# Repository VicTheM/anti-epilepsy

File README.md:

# Anti-Epilepsy Fast Response Device

## Hardware

### System schematic

### 3D PCB view

### Enclosure prototype

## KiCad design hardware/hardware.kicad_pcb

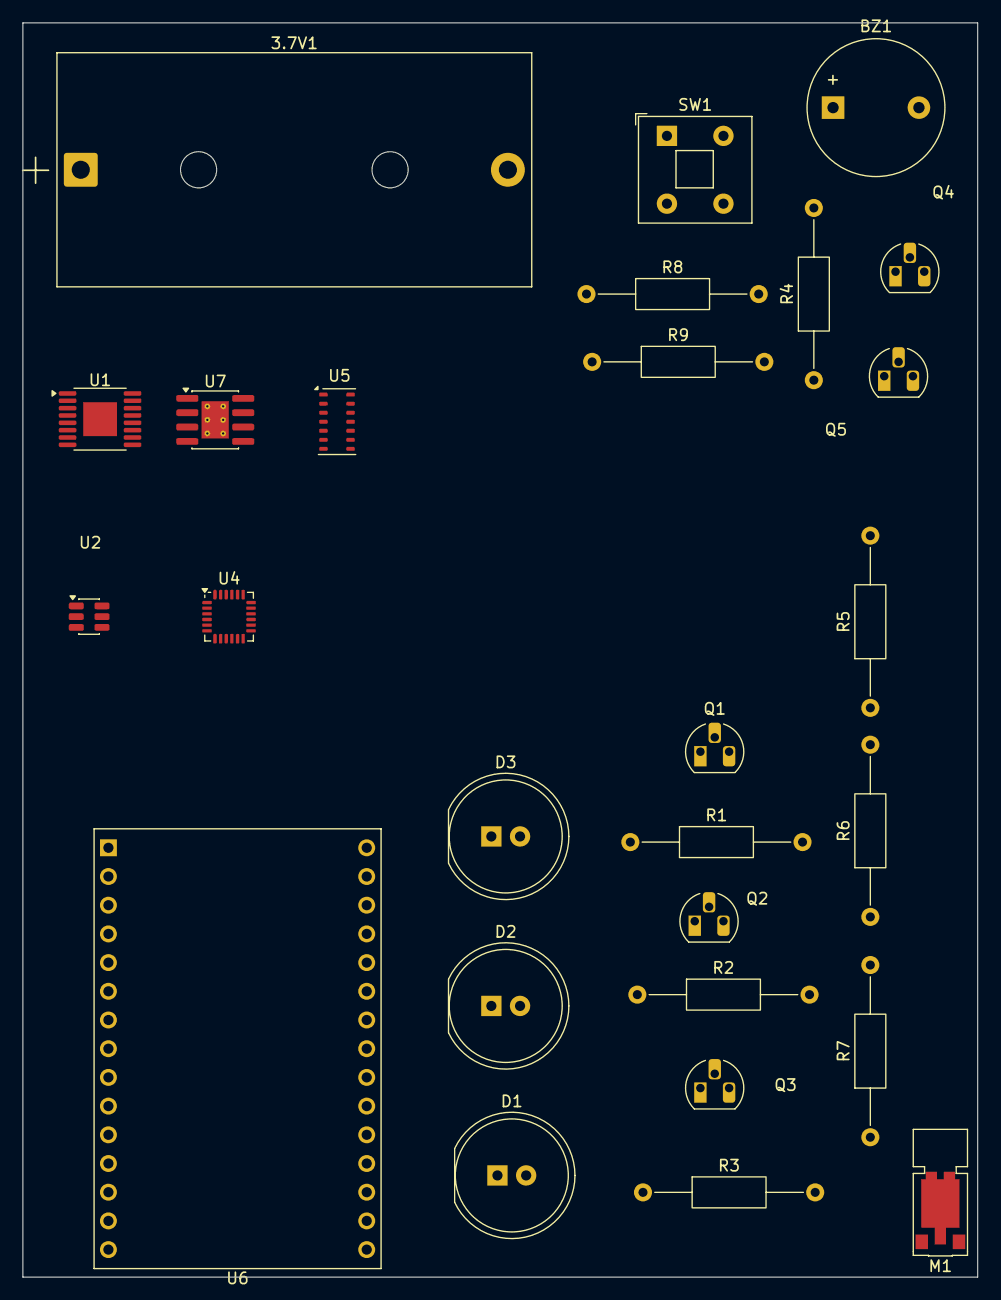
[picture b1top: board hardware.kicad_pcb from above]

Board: 2 copper layers, 84.5 x 111.0 mm, 27 parts (0 on the bottom side), 30 nets, no tracks yet.

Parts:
3.7V1: Battery; BatteryHolder_Bulgin_BX0123_1xCR123
BZ1: Buzzer; Buzzer_12x9.5RM7.6
D1, D2, D3: LED; LED_D10.0mm
M1: Motor_DC; Vybronics_VZ30C1T8219732L
Q1, Q2, Q3, Q5: 2N2219; TO-92L_HandSolder
Q4: Q_NPN_Darlington_BCEC; TO-92L_HandSolder
R1, R2, R6, R9: 220R; R_Axial_DIN0207_L6.3mm_D2.5mm_P15.24mm_Horizontal
R3, R4, R5, R7, R8: 1K; R_Axial_DIN0207_L6.3mm_D2.5mm_P15.24mm_Horizontal
SW1: SW_SPST; SW_Push_2P1T_Toggle_CK_PVA1xxH4xxxxxxV2
U1: A4954; TSSOP-16-1EP_4.4x5mm_P0.65mm_EP3x3mm
U2: TMP100; SOT-23-6
U4: MPU-6050; InvenSense_QFN-24_4x4mm_P0.5mm
U5: MAX30102; Maxim_OLGA-14_3.3x5.6mm_P0.8mm
U6: ESP32-S2-WROVER; ESP32-C3-DevKitM-1
U7: CN3158; SOIC-8-1EP_3.9x4.9mm_P1.27mm_EP2.41x3.3mm_ThermalVias

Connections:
+5V: BZ1.1 (+), D1.2 (A), D2.2 (A), D3.2 (A), M1.1 (+), SW1.2 (B), U2.4 (V+), U4.13 (VDD), U5.11 (VDD)
GND: 3.7V1.2 (-), Q4.3 (E), R1.2, R2.1, R6.2, R9.2, U2.2 (GND), U4.18 (GND), U5.12 (GND), U6.1 (GND), U6.26 (GND), U7.3 (GND), U7.9 (GND)
unnamed: 3.7V1.1 (+), U7.4 (VIN)
unnamed: BZ1.2 (-), Q1.3 (C)
unnamed: D1.1 (K), Q2.3 (C)
unnamed: D2.1 (K), Q3.3 (C)
unnamed: D3.1 (K), Q5.3 (C)
unnamed: M1.2 (-), Q4.2 (C)
unnamed: Q1.2 (B), R4.2
unnamed: Q1.1 (E), R2.2
unnamed: Q2.2 (B), R3.2
unnamed: Q2.1 (E), R1.1
unnamed: Q3.2 (B), R5.2
unnamed: Q3.1 (E), R6.1
unnamed: Q4.1 (B), R7.2
unnamed: Q5.2 (B), R8.2
unnamed: Q5.1 (E), R9.1
unnamed: SW1.1 (A), U7.5 (BAT)
unnamed: U1.1 (GND), U1.8 (GND), U1.17 (GND)
unnamed: U1.6 (IN1), U6.25 (IO26)
unnamed: U1.5 (IN2), U6.24 (IO21)
unnamed: U1.3 (IN3), U6.19 (IO16)
unnamed: U1.4 (IN4), U6.18 (IO15)
unnamed: U1.9 (VBB), U1.16 (VBB)
unnamed: U2.1 (SCL), U4.23 (SCL), U5.2 (SCL), U6.20 (IO17), U6.21 (IO18)
unnamed: U2.6 (SDA), U4.24 (SDA), U5.3 (SDA)
unnamed: U5.9 (VLED+), U5.10 (VLED+)
unnamed: R5.1, U6.27 (IO33)
unnamed: R8.1, U6.28 (IO34)
unnamed: R3.1, U6.29 (IO35)

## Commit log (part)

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2025-08-22 Circuit design setup
2025-08-22 Added libraries for accelerometer, gyrometer and heartbeat rate sensor
2025-08-26 Migrated hardware design from Kicad 9 to Proteus 9.1
2025-08-26 Documented the project
2025-08-26 Added pin conections
2025-08-26 Added png image
2025-08-31 Random tests
2025-09-03 Ported code for developemnt in the Arduino IDE using the Arduino framework
2025-09-04 Fixed compiler errors
2025-09-14 Added network layer
2025-09-14 CHECKPOINT: compile success, version 1
2025-09-14 Improved UI design
2025-10-03 CHECKPOINT: Proper working state
